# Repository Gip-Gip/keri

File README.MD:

# κερί

*The transmitter-equivalent of a candle*

## What is "κερί"?

κερί, pronounced carrie, is a small 1mhz AM transmitter meant to provide a
class B station for whatever radios you may have lying around.

## Why the name?

κερί, the Greek word for candle, was chosen as this transmitter, like a candle,
is "small, dim, and really only there to look cool".

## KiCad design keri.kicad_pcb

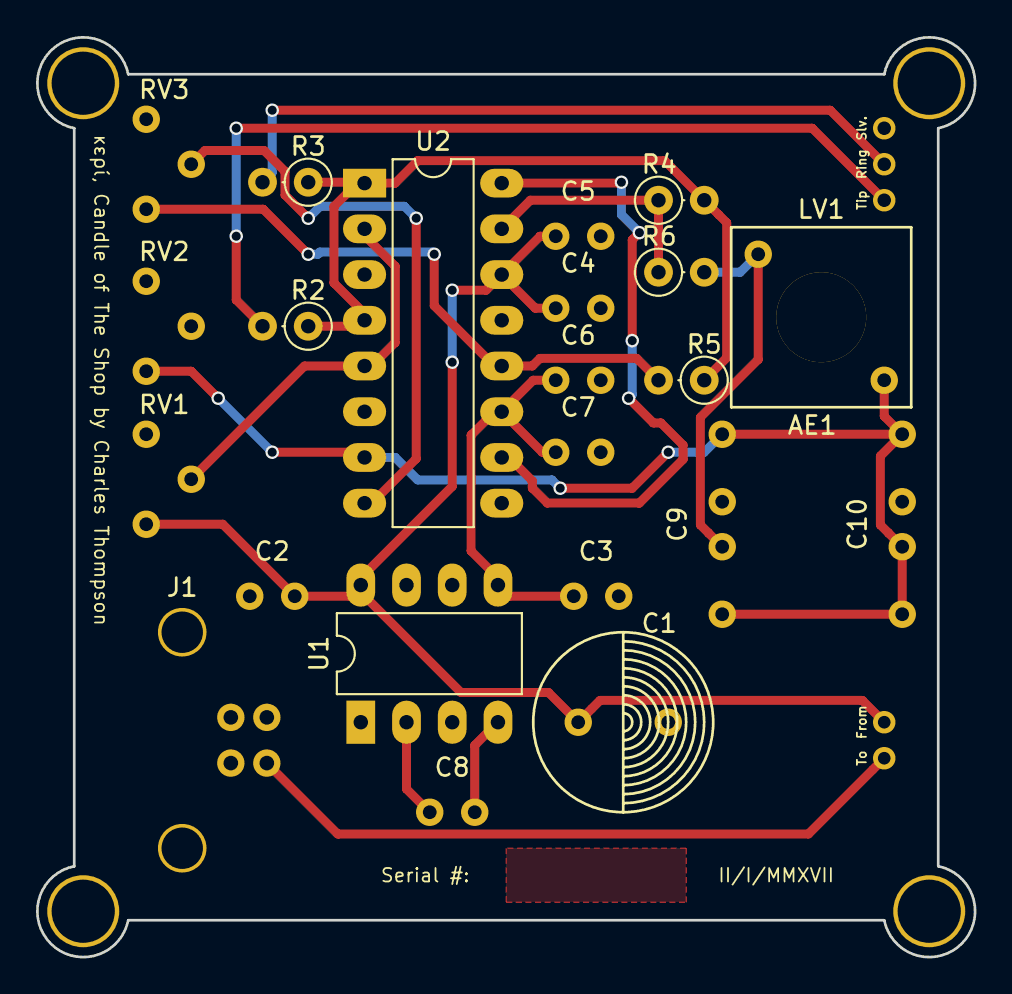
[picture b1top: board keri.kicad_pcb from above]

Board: 2 copper layers, 52.1 x 51.1 mm, 25 parts (0 on the bottom side), 16 nets.

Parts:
AE1: Antenna; mast
C1: 2200u; EEU-FS0J332B
C2, C3, C8: 1u; FA16C0G1H473JNU00
C4, C6: 0.1u; FA16C0G1H473JNU00
C5, C7: 4.7u; FA16C0G1H473JNU00
C9, C10: 47n; FA16C0G1H473JNU00
J1: PWR IN; USB_B
J2: Audio In; audio_in_panel
LV1: 708n; 143-11J12L
R2, R3: 2.2k; R_Axial_DIN0207_L6.3mm_D2.5mm_P2.54mm_Vertical
R4, R5: 1k; R_Axial_DIN0207_L6.3mm_D2.5mm_P2.54mm_Vertical
R6: 100; R_Axial_DIN0207_L6.3mm_D2.5mm_P2.54mm_Vertical
RV1: 10k Offset; 3362S-1-103LF
RV2: 10k Bleedoff; 3362S-1-103LF
RV3: 10k Trigger; 3362S-1-103LF
SW1: Pwr Sw; switch_panel
U1: TC7660H; DIP-8_W7.62mm_LongPads
U2: LT1260; DIP-16_W7.62mm_LongPads

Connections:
Earth: C1.2, C2.2, C3.1, C4.1, C5.1, C6.1, C7.1, C9.1, C10.1, J1.4, J1.5, J2.3, RV1.3, RV2.2, RV3.3, U1.3, U2.3, U2.6, U2.9, U2.13
unnamed: U2.10, U2.16
unnamed: R4.1, R6.1, U2.15
unnamed: RV1.2, U2.2, U2.5
unnamed: RV3.2, U2.8
unnamed: R2.1, R3.1, R4.2, R5.1, U2.1, U2.4
unnamed: AE1.1, C10.2, LV1.2, RV2.1, U2.7
unnamed: C8.1, U1.4
unnamed: C8.2, U1.2
unnamed: C9.2, LV1.1, R6.2
unnamed: J1.1, SW1.1
unnamed: J2.1, R2.2
unnamed: J2.2, R3.2
unnamed: R5.2, RV3.1, U2.12
VDD: C1.1, C2.1, C4.2, C5.2, RV1.1, SW1.2, U1.8, U2.14
VEE: C3.2, C6.2, C7.2, U1.5, U2.11

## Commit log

2018-02-03 Added the schematic files, PCB files, etc.
2018-02-03 Added footprints
2018-02-03 Rename #6_hole.kicad_mod to footprints.pretty/#6_hole.kicad_mod
2018-02-03 Rename 143-11J12L.kicad_mod to footprints.pretty/143-11J12L.kicad_mod
2018-02-03 Rename 3.5mm_jack.kicad_mod to footprints.pretty/3.5mm_jack.kicad_mod
2018-02-03 Rename 3362S-1-103LF.kicad_mod to footprints.pretty/3362S-1-103LF.kicad_mod
2018-02-03 Rename EEU-FS0J332B.kicad_mod to footprints.pretty/EEU-FS0J332B.kicad_mod
2018-02-03 Rename FA16C0G1H473JNU00.kicad_mod to footprints.pretty/FA16C0G1H473JNU00.kicad_mod
2018-02-03 Rename RV_Bourns_PVG3A.kicad_mod to footprints.pretty/RV_Bourns_PVG3A.kicad_mod
2018-02-03 Rename Trimmer_CB10V.kicad_mod to footprints.pretty/Trimmer_CB10V.kicad_mod
2018-02-03 Rename USB_B.kicad_mod to footprints.pretty/USB_B.kicad_mod
2018-02-03 Rename audio_in_panel.kicad_mod to footprints.pretty/audio_in_panel.kicad_mod
2018-02-03 Rename inductor_0604.kicad_mod to footprints.pretty/inductor_0604.kicad_mod
2018-02-04 Rename mast.kicad_mod to footprints.pretty/mast.kicad_mod
2018-02-04 Rename smd_usbb.kicad_mod to footprints.pretty/smd_usbb.kicad_mod
2018-02-04 Rename switch_panel.kicad_mod to footprints.pretty/switch_panel.kicad_mod
2018-02-04 Added documentation
2018-02-04 Create foo
2018-02-04 Set theme jekyll-theme-cayman
2018-02-04 Test
